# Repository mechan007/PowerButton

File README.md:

This is my first project on GitHub

This project was created out of the need to turn on and off a 3D printer with a button on the front panel. 
The emphasis was on powering the module directly from the mains voltage, also on the possible implementation
in existing devices, a button on the front panel and preventing shutdown by accidentally pressing the button.

The project is functional, but not finished (perhaps a prototype?),
it is intended for people who are familiar with this area.

Hopefully I will be able to continue and improve it.

I am also open to your questions, comments and suggestions,
but I warn you in advance that I am not able to respond immediately.

!!!Warning!!! This project uses high (mains) voltage! And can severely damage health, or cause death,
especially to people who do not know what they are doing! This project is not a final product,
it is not a recommendation or a guide! Everything you do with this, you do at your own risk!

Thank you for reading this far...

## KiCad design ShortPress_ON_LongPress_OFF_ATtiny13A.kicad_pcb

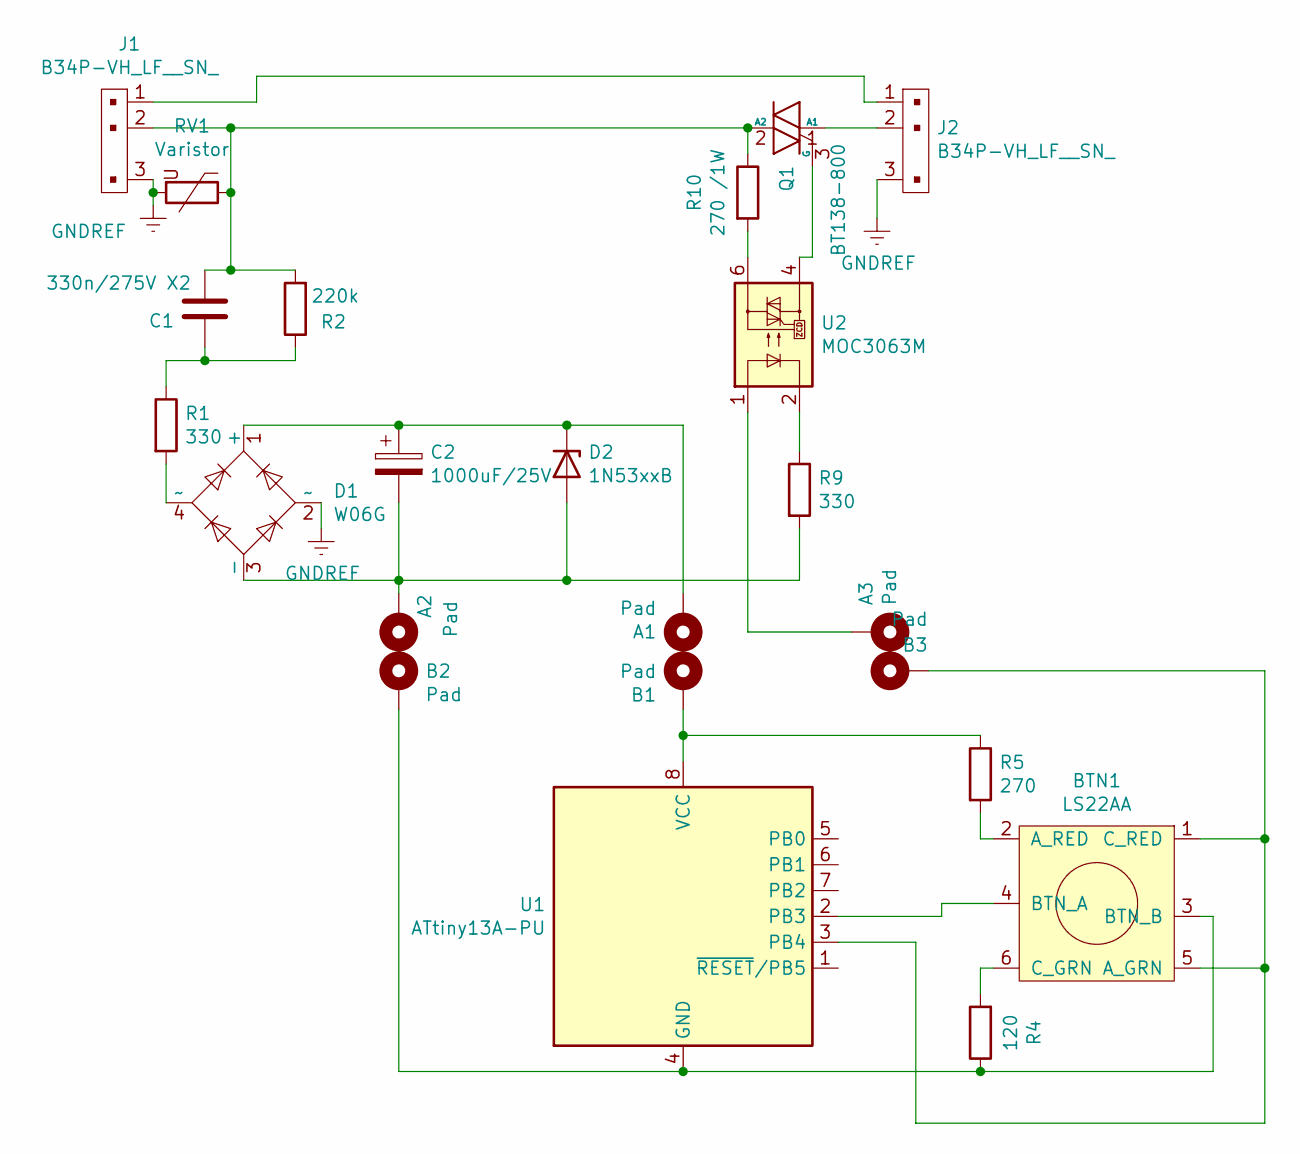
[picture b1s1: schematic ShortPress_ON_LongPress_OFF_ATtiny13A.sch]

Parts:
A1, A2, A3: Pad; PinHeader_1x01_P1.00mm_Vertical
B1, B2, B3: Pad; PinHeader_1x01_P1.00mm_Vertical
BTN1: LS22AA
C1: 330n/275V X2; C_Rect_L18.0mm_W8.0mm_P15.00mm_FKS3_FKP3
C2: 1000uF/25V; CP_Radial_D10.0mm_P5.00mm
D1: W06G; Diode_Bridge_Round_D9.8mm
D2: 1N53xxB; D_DO-201_P15.24mm_Horizontal
J1, J2: B34P-VH_LF__SN_; PinHeader_1x3_4_P3.96mm_Drill1.6mm
Q1: BT138-800; TO-220-3_Vertical
R1, R9: 330; R_Axial_DIN0207_L6.3mm_D2.5mm_P10.16mm_Horizontal
R2: 220k; R_Axial_DIN0207_L6.3mm_D2.5mm_P10.16mm_Horizontal
R4: 120; R_Axial_DIN0207_L6.3mm_D2.5mm_P10.16mm_Horizontal
R5: 270; R_Axial_DIN0207_L6.3mm_D2.5mm_P10.16mm_Horizontal
R10: 270 /1W; R_Axial_DIN0414_L11.9mm_D4.5mm_P15.24mm_Horizontal
RV1: Varistor; RV_Disc_D15.5mm_W4.8mm_P7.5mm
U1: ATtiny13A-PU; DIP-8_W7.62mm
U2: MOC3063M; DIP-6_W7.62mm

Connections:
GNDREF: D1.2 (~~), J1.3, J2.3, RV1.2
unnamed: A1.1, C2.1, D1.1 (+), D2.1 (K)
unnamed: A2.1, C2.2, D1.3 (-), D2.2 (A), R9.2
unnamed: A3.1, U2.1
unnamed: B1.1, R5.1, U1.8 (VCC)
unnamed: B2.1, BTN1.3 (BTN_B), R4.1, U1.4 (GND)
unnamed: B3.1, BTN1.1 (C_RED), BTN1.5 (A_GRN), U1.3 (PB4)
unnamed: BTN1.2 (A_RED), R5.2
unnamed: BTN1.4 (BTN_A), U1.2 (PB3)
unnamed: BTN1.6 (C_GRN), R4.2
unnamed: C1.1, R1.1, R2.1
unnamed: C1.2, J1.2, Q1.2 (A2), R2.2, R10.1, RV1.1
unnamed: D1.4 (~~), R1.2
unnamed: J1.1, J2.1
unnamed: J2.2, Q1.1 (A1)
unnamed: Q1.3 (G), U2.4
unnamed: R9.1, U2.2
unnamed: R10.2, U2.6

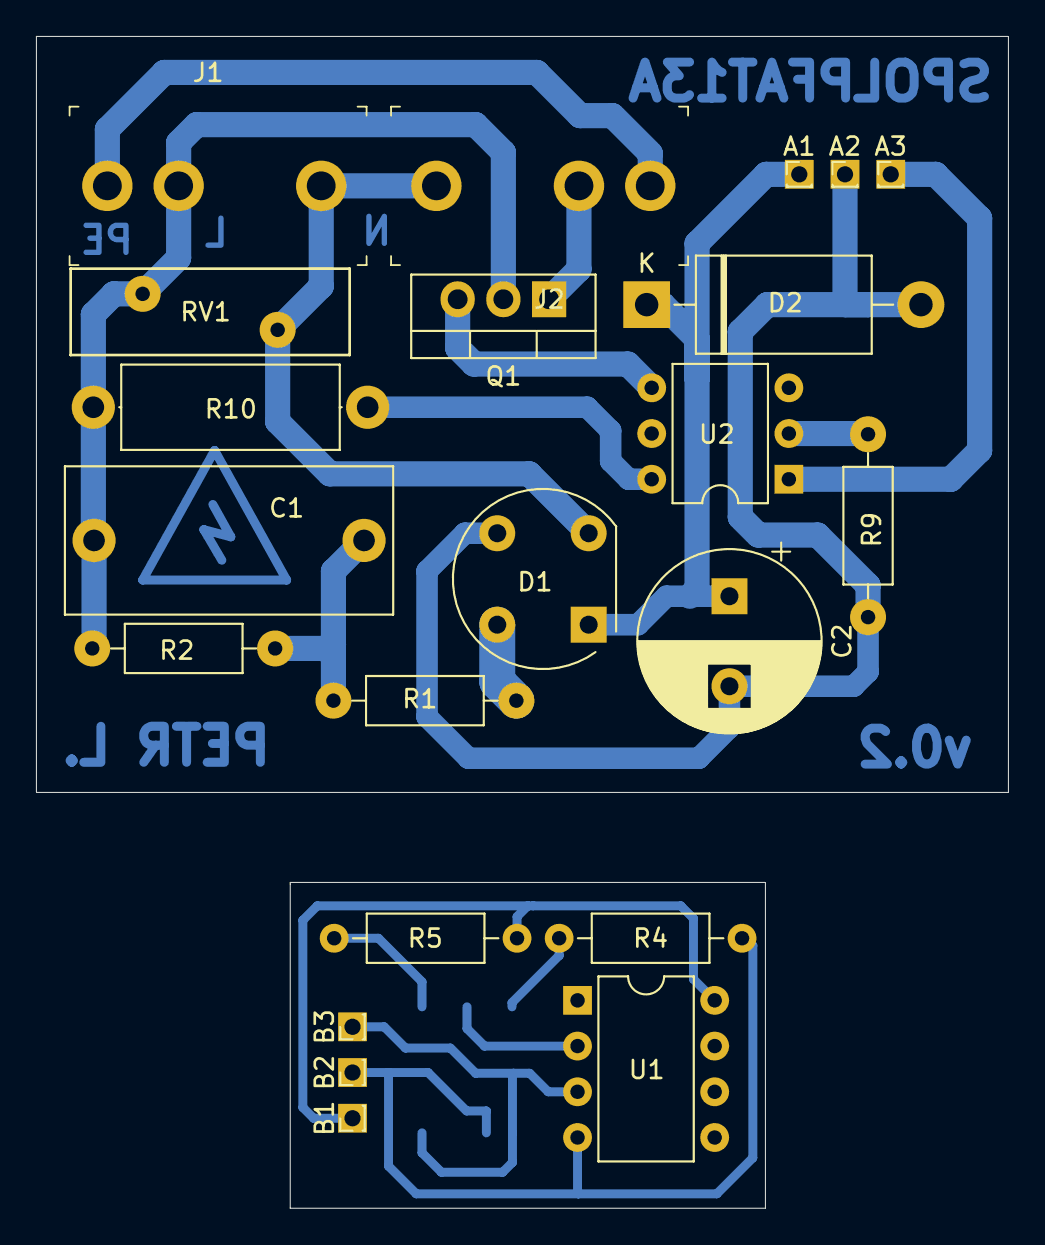
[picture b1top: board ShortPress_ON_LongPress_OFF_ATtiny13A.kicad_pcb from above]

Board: 2 copper layers, 54.0 x 65.1 mm, 23 parts (1 on the bottom side), 18 nets.
